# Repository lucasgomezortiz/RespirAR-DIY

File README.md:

# RespirAR DIY
###### Ante la urgencia y necesidad de los hospitales y centros de salud que combaten dia a dia con la Pandemia Covid-19(Coronavirus) buscamos la forma de generar un proyecto para aliviar la situacion actual, uno de los equipos mas necesiarios para combatir esta pandemia son los repiradores artifiales y de bajo presupuesto.
 
### EL PROYECTO ESTA EN FASE DESARROLLO
###### Toda ayuda es bienvenida para el desarrollo

Thingiverse: https://www.thingiverse.com/thing:4232749
fusion360: 

# Cualquier duda, sugerencia o aporte
Grupo de [facebook](https://www.facebook.com/groups/respiradormaker/) 
Instagram [@rejuntamaker](https://www.instagram.com/rejuntamaker/) [@lucasgomezortiz](https://www.instagram.com/lucasgomezortiz/)
### Este proyecto nace de [Reespirator](https://twitter.com/ReesistenciaT)

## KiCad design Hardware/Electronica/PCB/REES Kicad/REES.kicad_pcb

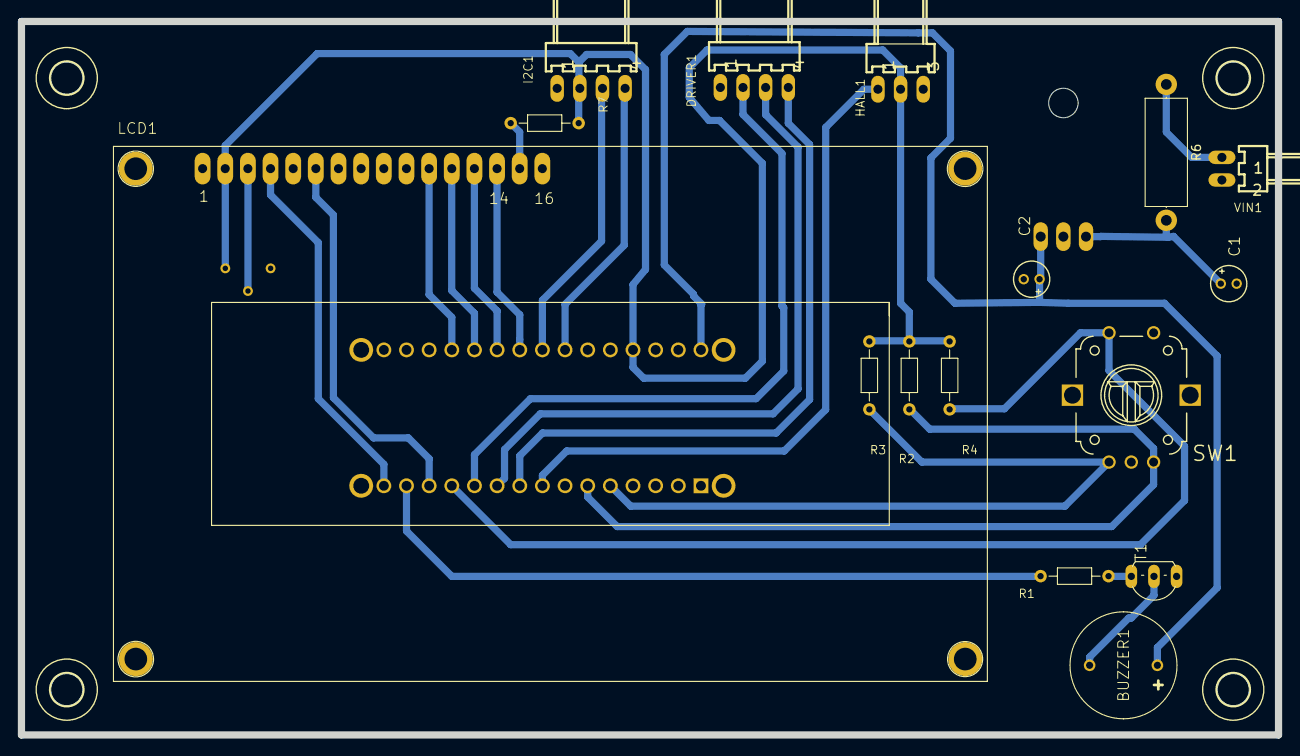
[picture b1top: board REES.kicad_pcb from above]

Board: 2 copper layers, 141.0 x 80.0 mm, 23 parts (0 on the bottom side), 25 nets.

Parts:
ARDUINO1: ARD-NANO30NP; ARDNANO30NP
BUZZER1: TMB12A05
C1: 330n; E1,8-4
C2: 100n; E1,8-4
DRIVER1: 22-?-0405-7048; 7395-04
H1, H2, H3, H4: HOLES_MOUNT-HOLE3.6; HOLES_3,6
HALL1: 22-?-0305-7038; 7395-03
I2C1: 22-?-0405-7048; 7395-04
LCD1: L2034-T
R1: 1k; R_Axial_DIN0204_L3.6mm_D1.6mm_P7.62mm_Horizontal
R2, R3, R4: 10k; R_Axial_DIN0204_L3.6mm_D1.6mm_P7.62mm_Horizontal
R5: 15k; RTRIM3339P
R6: 10R; R_Axial_DIN0414_L11.9mm_D4.5mm_P15.24mm_Horizontal
R7: 10R; R_Axial_DIN0204_L3.6mm_D1.6mm_P7.62mm_Horizontal
REGULADOR1: LINEAR_7812T; LINEAR_TO220H
SW1: ENCODER_SW1-PEC12; PEC12_INCREMENTAL_ENCODER
T1: 2SC945; TO92-ECB
VIN1: 22-?-0205-7028; 7395-02

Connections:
+5V: ARDUINO1.19, HALL1.2, I2C1.2, LCD1.2, R2.2, R3.2, R4.2, R5.3, R7.1
+12V: ARDUINO1.16, BUZZER1.1, C2.+, REGULADOR1.3
+24V: C1.+, R6.2, REGULADOR1.1
/BUZZ: ARDUINO1.14, R1.1
/CLK: ARDUINO1.5, R3.1, SW1.A
/D4: ARDUINO1.27, LCD1.11
/D5: ARDUINO1.26, LCD1.12
/D6: ARDUINO1.25, LCD1.13
/D7: ARDUINO1.24, LCD1.14
/DIR: ARDUINO1.10, DRIVER1.3
/DT: ARDUINO1.6, R2.1, SW1.B
/E: ARDUINO1.13, LCD1.6
/ENA: ARDUINO1.11, DRIVER1.2
/HALL: ARDUINO1.8, HALL1.1
/PUL: ARDUINO1.9, DRIVER1.4
/RS: ARDUINO1.15, LCD1.4
/SCL: ARDUINO1.22, I2C1.4
/SDA: ARDUINO1.23, I2C1.3
/SW: ARDUINO1.12, R4.1, SW1.P1
GND: ARDUINO1.4, ARDUINO1.17, C1.-, C2.-, DRIVER1.1, HALL1.3, I2C1.1, LCD1.1, LCD1.5, LCD1.16, R5.1, REGULADOR1.2, SW1.C, SW1.P2, T1.E, VIN1.2
unnamed: BUZZER1.2, T1.C
unnamed: LCD1.3, R5.2
unnamed: LCD1.15, R7.2
unnamed: R1.2, T1.B
unnamed: R6.1, VIN1.1

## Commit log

2020-03-21 README
2020-03-21 Subiendo contenido de Reespirator
    Subo el Git de Reespirartor
2020-03-21 Informacion tecnica para imprimir
    Adjunto los datos tecnicos y perfiles para la impresion
2020-03-21 Mejoras varias
    -Eliminacion de la pieza Acople
    -Correcion un error de anguno en el diseño
    -Se rediseño la leva completamente desde cero, manteniendo dimenciones originales en tamaño, el canto fue rediseñado con un radio de 5mm para que se almolde al rodamiento del brazo.
    -se intrego un sistema de acople directo, elimiando 4 tornillos, solo requiere uno para presionar el motor.
2020-03-21 Escuadras
    Para sujertar el respirador al chasis, importante respetar la posicion de impresion
2020-03-21 Placas a y b compatibles con las escuadras
    agregue un sistema de encastre para las escuadras
2020-03-21 Reorganizacion de carpetas
    Divido los diseños entre pruebas y finales, recomiendo esperar a que las piezas sean aprobadas
2020-03-22 Update Presionador.stl
    Rediseño para evitar soporte de impresion
2020-03-22 Listo
    La leva ya se encuentra en diseño final
2020-03-22 Agrego el archivo editable del Fusion360
    En este archivo se encuentra el diseño con todas sus revisiones, el chasis esta en progreso
2020-03-22 Leva Final
2020-03-22 Moviendo archivos finalizados
    Archivos listos para imprimir
2020-03-22 Brazo final
    Se agrego un tope al rodamiento 608
2020-03-25 Update Presionador.stl
    Arreglo en algunos vertices
